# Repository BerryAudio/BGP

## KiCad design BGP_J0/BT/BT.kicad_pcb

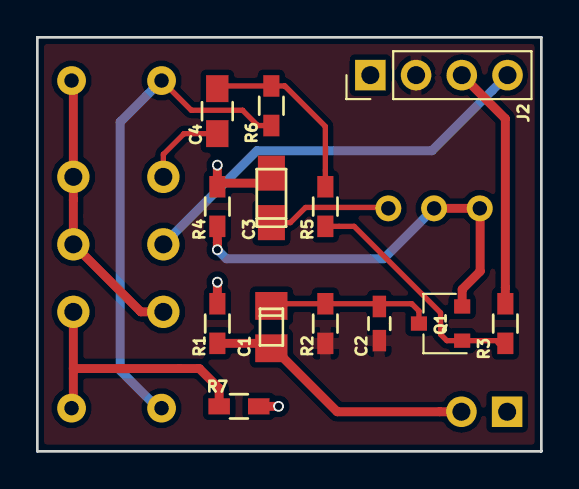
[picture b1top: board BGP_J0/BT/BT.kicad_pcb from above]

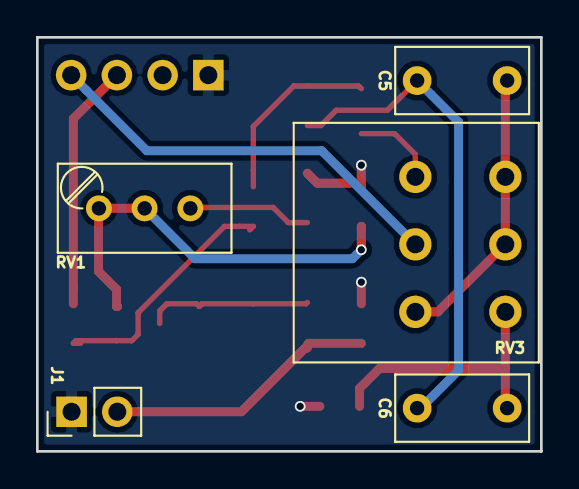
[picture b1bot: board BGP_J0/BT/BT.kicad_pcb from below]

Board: 2 copper layers, 28.0 x 23.0 mm, 18 parts (5 on the bottom side), 14 nets.

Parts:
C1: 0.1u; TantalC_SizeR_EIA-2012
C2: 270p; C_0603_HandSoldering
C3: 47u; TantalC_SizeS_EIA-3216
C4: 2700p; C_0805_HandSoldering
C5: 1u; C_Rect_L7.2mm_W3.5mm_P5.00mm_FKS2_FKP2_MKS2_MKP2
C6: 0.33u; C_Rect_L7.2mm_W3.5mm_P5.00mm_FKS2_FKP2_MKS2_MKP2
J1: Conn_01x02_Male; PinHeader_1x02_P2.54mm_Vertical
J2: Conn_01x04_Male; PinHeader_1x04_P2.54mm_Vertical
Q1: MMBF5457; SC-59
R1: NF; R_0603_HandSoldering
R2: 1Meg; R_0603_HandSoldering
R3, R6: 10k; R_0603_HandSoldering
R4: 3.9k; R_0603_HandSoldering
R5: 1k; R_0603_HandSoldering
R7: 1.8k; R_0603_HandSoldering
RV1: POT; Potentiometer_Trimmer_Bourns_3296W
RV3: DUAL_POT; Potentiometer_Alpha_Double_Vertical_Dual_Shaft

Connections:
/IN: C1.2, J1.2, R1.1
/RV_1: C6.2, R7.1, RV3.1
/RV_2: C5.2, RV3.2, RV3.3, RV3.4
/RV_5: J2.4, RV3.5
/RV_6: C4.2, RV3.6
/Vref: C2.2, J2.2, R2.2
Earth: C3.2, J1.1, J2.1, R1.2, R4.2, R7.2
unnamed: C1.1, C2.1, Q1.3, R2.1
unnamed: C3.1, RV1.3
unnamed: C4.1, R5.1, R6.1
unnamed: C5.1, C6.1, R6.2
unnamed: Q1.1, R3.2, R5.2
unnamed: Q1.2, R4.1, RV1.1, RV1.2
VCC: J2.3, R3.1

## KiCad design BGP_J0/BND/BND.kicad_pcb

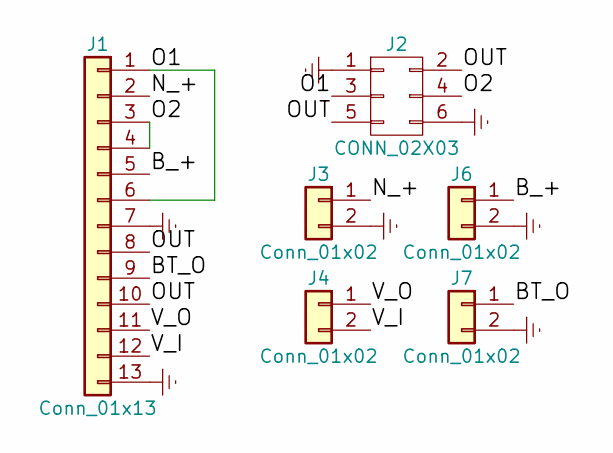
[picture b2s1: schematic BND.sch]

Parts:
J1: Conn_01x13; Bournes_Blend_PP
J2: CONN_02X03; Pin_Header_Straight_2x03
J3, J6: Conn_01x02; TerminalBlock_Phoenix_MPT-2.54mm_2pol
J4, J7: Conn_01x02; Pin_Header_Straight_1x02

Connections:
/BT_O: J1.9, J7.1
/B_+: J1.5, J6.1
/N_+: J1.2, J3.1
/O1: J1.1, J1.6, J2.3
/O2: J1.3, J1.4, J2.4
/OUT: J1.8, J1.10, J2.2, J2.5
/V_I: J1.12, J4.2
/V_O: J1.11, J4.1
Earth: J1.7, J1.13, J2.1, J2.6, J3.2, J6.2, J7.2

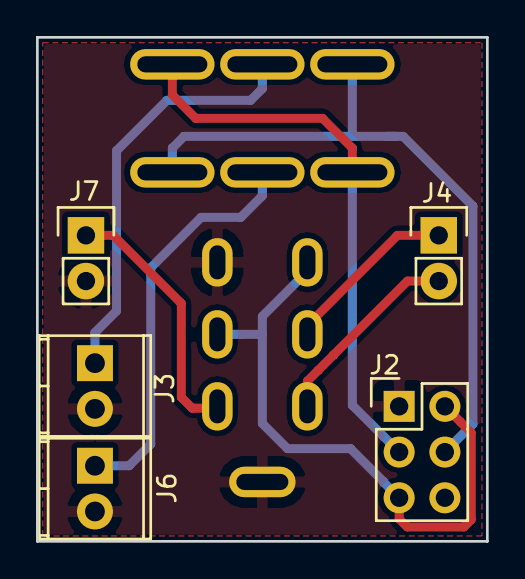
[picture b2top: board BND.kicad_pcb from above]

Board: 2 copper layers, 25.0 x 28.0 mm, 6 parts (1 on the bottom side), 9 nets.

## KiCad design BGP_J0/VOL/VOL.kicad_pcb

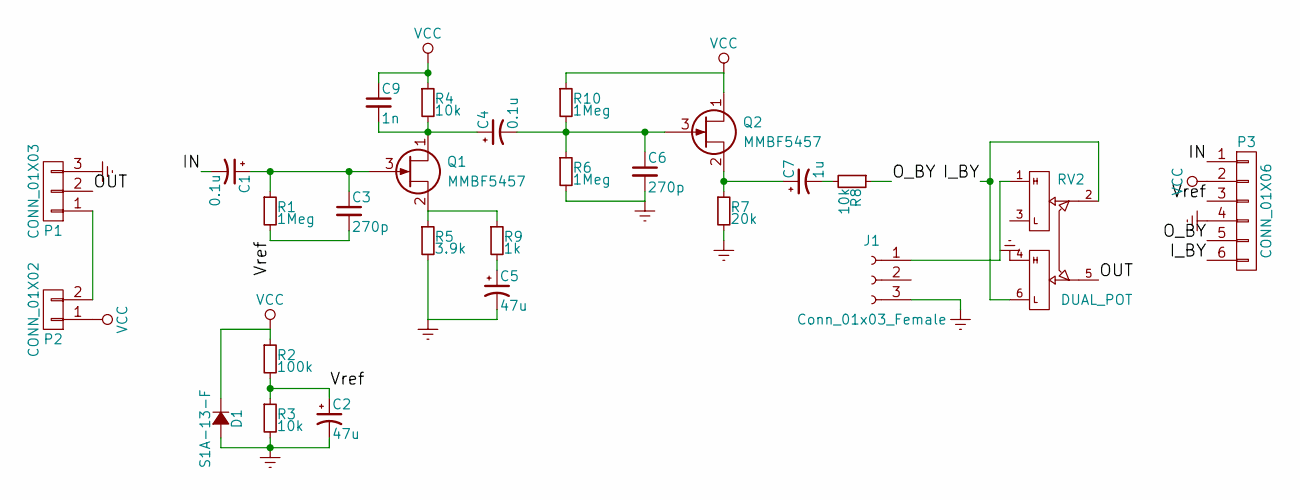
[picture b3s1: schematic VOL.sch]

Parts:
C1, C4: 0.1u; TantalC_SizeR_EIA-2012
C2, C5: 47u; TantalC_SizeS_EIA-3216
C3, C6: 270p; C_0603_HandSoldering
C7: 1u; TantalC_SizeR_EIA-2012
C9: 1n; C_0805
D1: S1A-13-F; SMA_Standard
J1: Conn_01x03_Female; Pin_Header_Straight_1x03_Pitch2.54mm
P1: CONN_01X03; TerminalBlock_Pheonix_MPT-2.54mm_3pol
P2: CONN_01X02; TerminalBlock_Pheonix_MPT-2.54mm_2pol
P3: CONN_01X06; Pin_Header_Straight_1x06
Q1, Q2: MMBF5457; SC-59
R1, R6, R10: 1Meg; R_0603_HandSoldering
R2: 100k; R_0603_HandSoldering
R3, R4, R8: 10k; R_0603_HandSoldering
R5: 3.9k; R_0603_HandSoldering
R7: 20k; R_0603_HandSoldering
R9: 1k; R_0603_HandSoldering
RV2: DUAL_POT; Potentiometer_Alpha_Double_Vertical_Dual_Shaft

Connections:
/IN: C1.2, P3.1
/I_BY: P3.6, RV2.2, RV2.6
/OUT: P1.2, RV2.5
/O_BY: P3.5, R8.1
/Vref: C2.1, C3.2, P3.3, R1.2, R2.2, R3.1
Earth: C2.2, C5.2, C6.2, D1.2 (A), J1.3, P1.3, P3.4, R3.2, R5.2, R6.2, R7.2, RV2.4
unnamed: C1.1, C3.1, Q1.3 (G), R1.1
unnamed: C4.1, C9.2, Q1.1 (D), R4.2
unnamed: C4.2, C6.1, Q2.3 (G), R6.1, R10.2
unnamed: C5.1, R9.2
unnamed: C7.1, Q2.2 (S), R7.1
unnamed: C7.2, R8.2
unnamed: J1.1, RV2.1
unnamed: P1.1, P2.2
unnamed: Q1.2 (S), R5.1, R9.1
VCC: C9.1, D1.1 (K), P2.1, P3.2, Q2.1 (D), R2.1, R4.1, R10.1

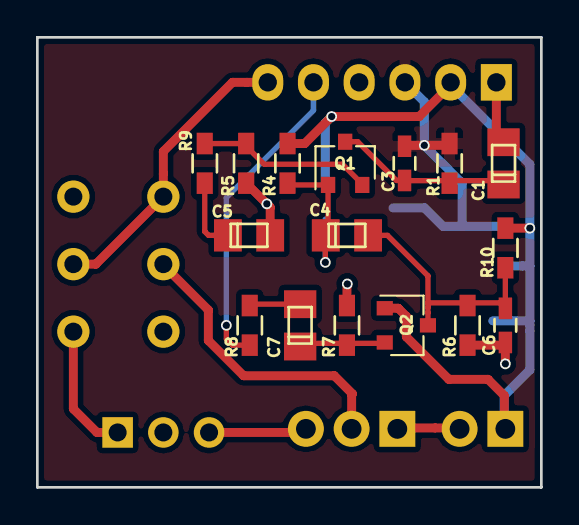
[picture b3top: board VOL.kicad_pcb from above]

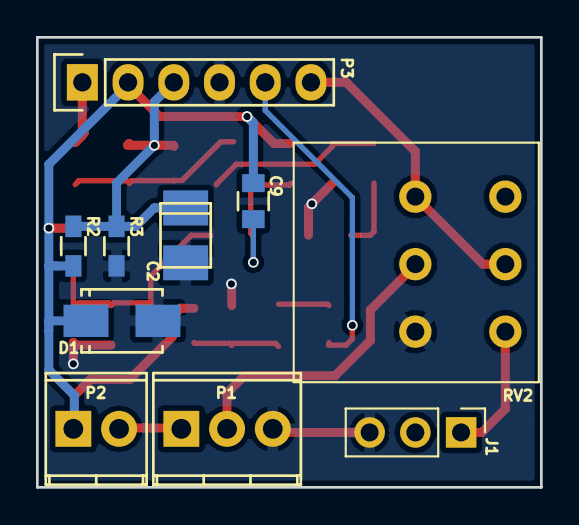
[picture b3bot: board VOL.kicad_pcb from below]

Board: 2 copper layers, 28.0 x 25.0 mm, 26 parts (10 on the bottom side), 16 nets.

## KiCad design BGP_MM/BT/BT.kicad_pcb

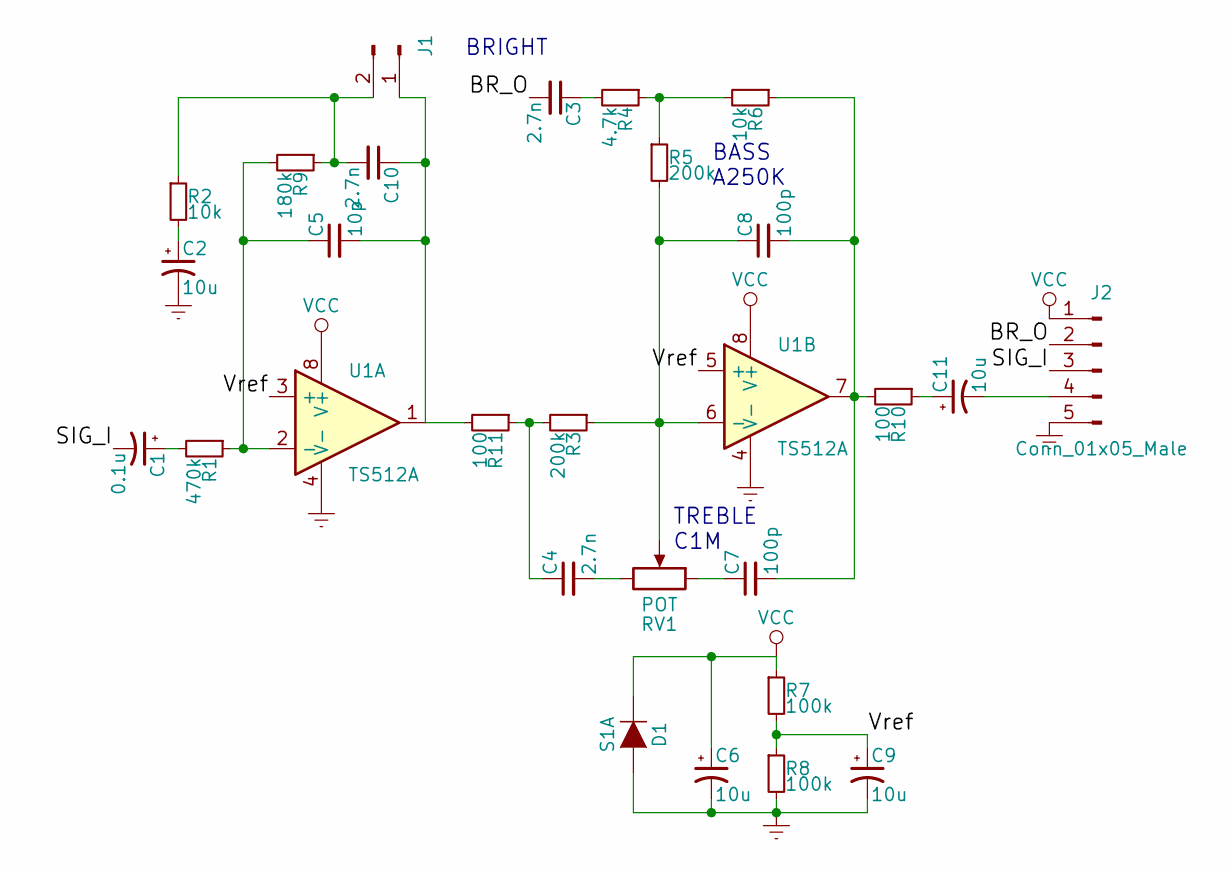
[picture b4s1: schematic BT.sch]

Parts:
C1: 0.1u; C_0805
C2, C11: 10u; C_0805
C3, C4, C10: 2.7n; C_0805
C5: 10p; C_0603_HandSoldering
C6, C9: 10u; C_1206
C7, C8: 100p; C_0603_HandSoldering
D1: S1A; SMA_Standard
J1: Conn_01x02_Male; Pin_Header_Straight_1x02
J2: Conn_01x05_Male; Pin_Header_Straight_1x05_Pitch2.54mm
R1: 470k; C_0603_HandSoldering
R2, R6: 10k; C_0603_HandSoldering
R3, R5: 200k; C_0603_HandSoldering
R4: 4.7k; C_0603_HandSoldering
R7, R8: 100k; C_0603_HandSoldering
R9: 180k; C_0603_HandSoldering
R10, R11: 100; C_0603_HandSoldering
RV1: POT; Potentiometer_Alpha_RV16
U1: TS512A; SOIC-8-N

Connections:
/BR_O: C3.2, J2.2
/SIG_I: C1.2, J2.3
/Vref: C9.1, R7.2, R8.1, U1.3 (+), U1.5 (+)
Earth: C2.2, C6.2, C9.2, D1.2 (A), J2.5, R8.2, U1.4 (V-)
unnamed: C1.1, R1.2
unnamed: C2.1, R2.2
unnamed: C3.1, R4.2
unnamed: C4.1, R3.2, R11.1
unnamed: C4.2, RV1.3
unnamed: C5.1, R1.1, R9.2, U1.2 (-)
unnamed: C7.1, RV1.1
unnamed: C7.2, C8.2, R6.1, R10.2, U1.7
unnamed: C8.1, R3.1, R5.2, RV1.2, U1.6 (-)
unnamed: C5.2, C10.1, J1.1, R11.2, U1.1
unnamed: C10.2, J1.2, R2.1, R9.1
unnamed: C11.1, R10.1
unnamed: C11.2, J2.4
unnamed: R4.1, R5.1, R6.2
VCC: C6.1, D1.1 (K), J2.1, R7.1, U1.8 (V+)

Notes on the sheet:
BRIGHT
BASS A250K
TREBLE C1M

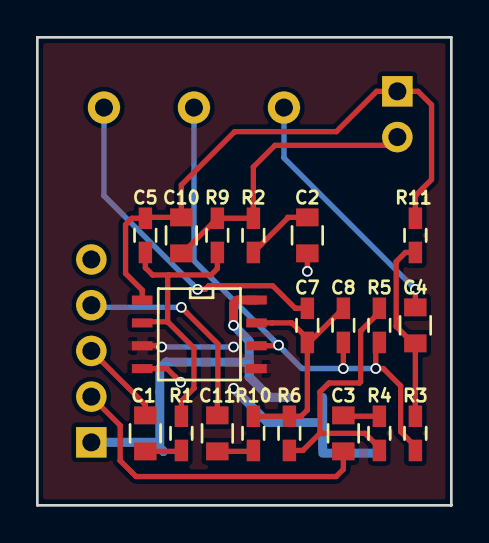
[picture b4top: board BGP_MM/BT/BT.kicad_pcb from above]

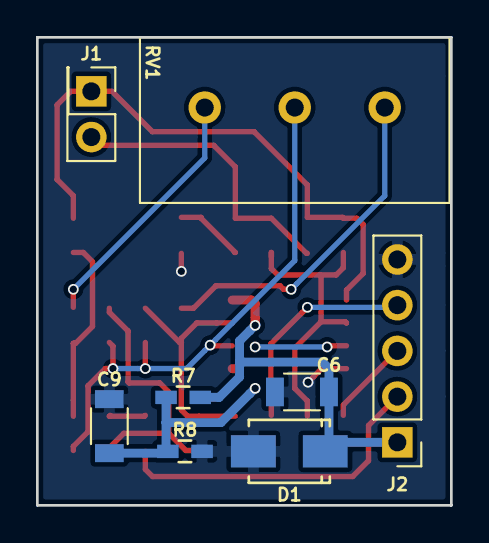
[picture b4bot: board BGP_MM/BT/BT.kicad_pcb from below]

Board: 2 copper layers, 23.0 x 26.0 mm, 27 parts (8 on the bottom side), 19 nets.

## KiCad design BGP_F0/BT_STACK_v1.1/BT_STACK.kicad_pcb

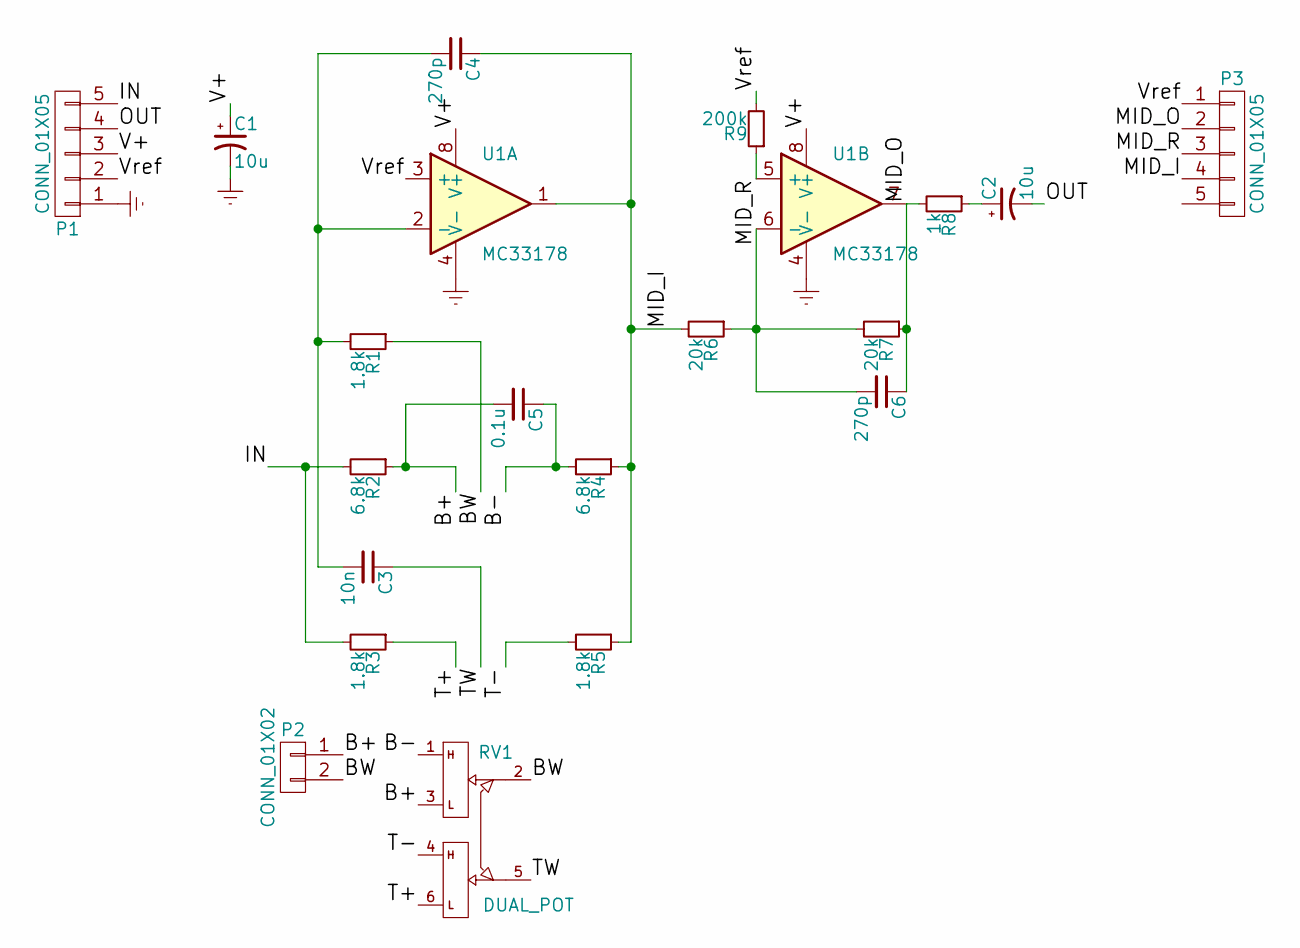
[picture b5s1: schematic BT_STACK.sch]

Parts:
C1: 10u; C_1206_HandSoldering
C2: 10u; C_0805_HandSoldering
C3: 10n; C_0805_HandSoldering
C4, C6: 270p; C_0603_HandSoldering
C5: 0.1u; C_0805_HandSoldering
P1, P3: CONN_01X05; Pin_Header_Straight_1x05
P2: CONN_01X02; Pin_Header_Straight_1x02_Pitch2.54mm
R1, R3, R5: 1.8k; R_0603_HandSoldering
R2, R4: 6.8k; R_0603_HandSoldering
R6, R7: 20k; R_0603_HandSoldering
R8: 1k; R_0603_HandSoldering
R9: 200k; R_0603_HandSoldering
RV1: DUAL_POT; Potentiometer_Alpha_Double_Vertical_Dual_Shaft
U1: MC33178; SOIC-8_3.9x4.9mm_Pitch1.27mm

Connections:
/B+: C5.2, P2.1, R2.1, RV1.3
/B-: C5.1, R4.2, RV1.1
/BW: P2.2, R1.1, RV1.2
/IN: P1.5, R2.2, R3.2
/MID_I: C4.1, P3.4, R4.1, R5.1, R6.2, U1.1
/MID_O: C6.1, P3.2, R7.1, R8.2, U1.7
/MID_R: P3.3, R9.1, U1.5 (+)
/OUT: C2.2, P1.4
/T+: R3.1, RV1.6
/T-: R5.2, RV1.4
/TW: C3.1, RV1.5
/V+: C1.1, P1.3, U1.8 (V+)
/Vref: P1.2, P3.1, R9.2, U1.3 (+)
Earth: C1.2, P1.1, U1.4 (V-)
unnamed: C2.1, R8.1
unnamed: C3.2, C4.2, R1.2, U1.2 (-)
unnamed: C6.2, R6.1, R7.2, U1.6 (-)

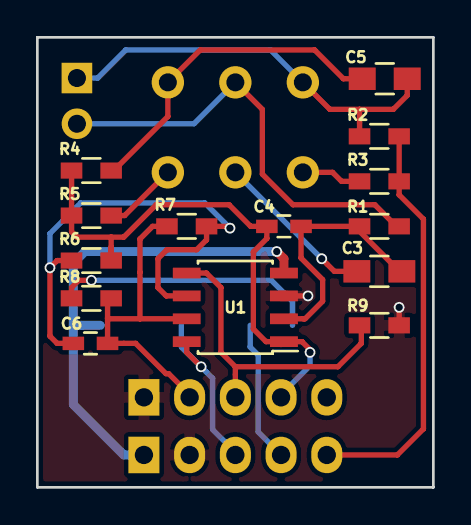
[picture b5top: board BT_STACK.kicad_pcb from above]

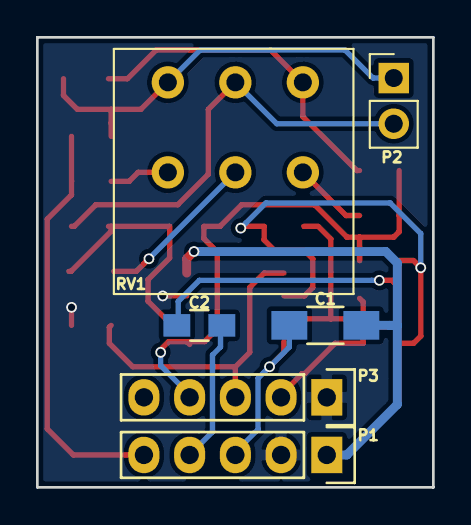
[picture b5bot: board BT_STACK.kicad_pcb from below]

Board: 2 copper layers, 22.0 x 25.0 mm, 20 parts (6 on the bottom side), 17 nets.

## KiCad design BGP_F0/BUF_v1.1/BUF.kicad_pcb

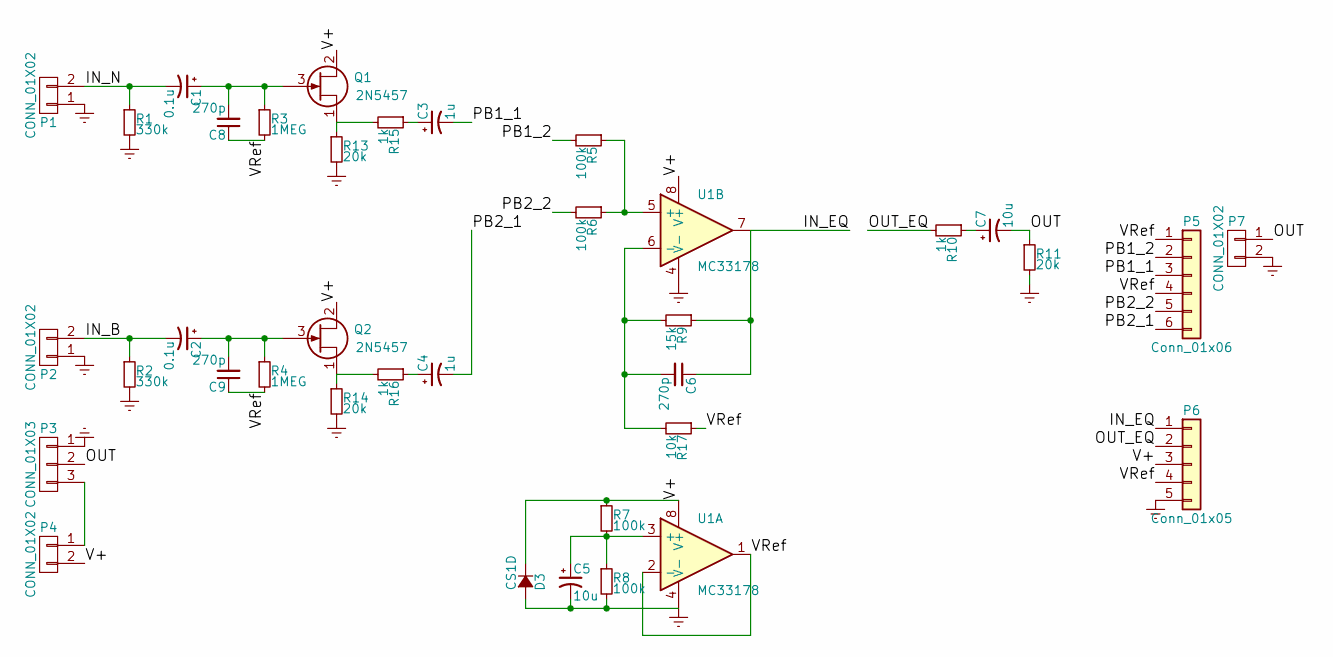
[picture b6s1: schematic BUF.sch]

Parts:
C1, C2: 0.1u; C_0805
C3, C4: 1u; C_0805
C5: 10u; C_1206
C6, C8, C9: 270p; C_0603
C7: 10u; C_0805
D3: CS1D; D_SMA
P1, P2, P4: CONN_01X02; TerminalBlock_Pheonix_MPT-2.54mm_2pol
P3: CONN_01X03; TerminalBlock_Pheonix_MPT-2.54mm_3pol
P5: Conn_01x06; Potentiometer_Alpha_Double_Vertical_Dual_Shaft
P6: Conn_01x05; Pin_Header_Straight_1x05
P7: CONN_01X02; Pin_Header_Straight_1x02
Q1, Q2: 2N5457; SC-59
R1, R2: 330k; R_0603
R3, R4: 1MEG; R_0603
R5, R6, R7, R8: 100k; R_0603
R9: 15k; R_0603
R10, R15, R16: 1k; R_0603
R11, R13, R14: 20k; R_0603
R17: 10k; R_0603
U1: MC33178; SOIC-8_3.9x4.9mm_Pitch1.27mm

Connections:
/IN_B: C2.2, P2.2, R2.1
/IN_EQ: C6.1, P6.1, R9.1, U1.7
/IN_N: C1.2, P1.2, R1.1
/OUT: C7.2, P3.2, P7.1, R11.1
/OUT_EQ: P6.2, R10.2
/PB1_1: C3.2, P5.3
/PB1_2: P5.2, R5.2
/PB2_1: C4.2, P5.6
/PB2_2: P5.5, R6.2
/V+: D3.1 (K), P4.2, P6.3, Q1.2 (D), Q2.2 (D), R7.1, U1.8 (V+)
/VRef: C8.1, C9.1, P5.1, P5.4, P6.4, R3.2, R4.2, R17.1, U1.1, U1.2 (-)
Earth: C5.2, D3.2 (A), P1.1, P2.1, P3.1, P6.5, P7.2, R1.2, R2.2, R8.2, R11.2, R13.2, R14.2, U1.4 (V-)
unnamed: C1.1, C8.2, Q1.3 (G), R3.1
unnamed: C2.1, C9.2, Q2.3 (G), R4.1
unnamed: C3.1, R15.1
unnamed: C4.1, R16.1
unnamed: C5.1, R7.2, R8.1, U1.3 (+)
unnamed: C6.2, R9.2, R17.2, U1.6 (-)
unnamed: C7.1, R10.1
unnamed: P3.3, P4.1
unnamed: Q1.1 (S), R13.1, R15.2
unnamed: Q2.1 (S), R14.1, R16.2
unnamed: R5.1, R6.1, U1.5 (+)

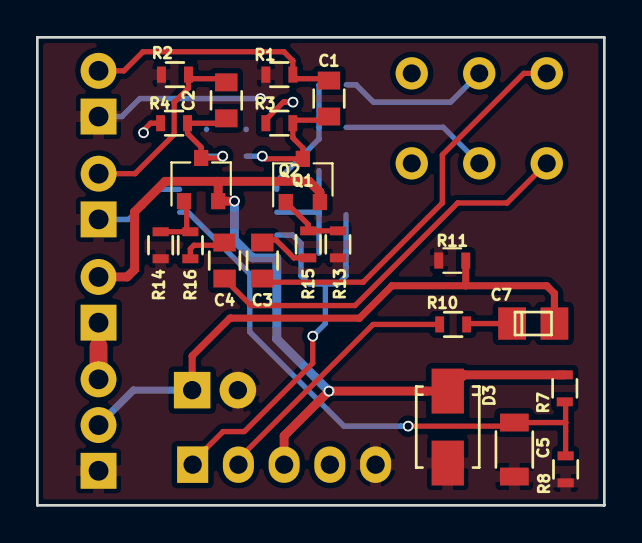
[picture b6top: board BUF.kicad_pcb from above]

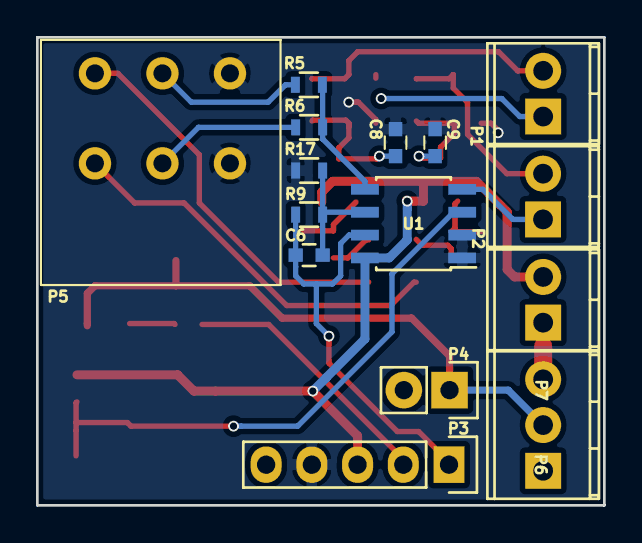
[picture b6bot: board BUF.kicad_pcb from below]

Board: 2 copper layers, 31.5 x 26.0 mm, 36 parts (15 on the bottom side), 23 nets.

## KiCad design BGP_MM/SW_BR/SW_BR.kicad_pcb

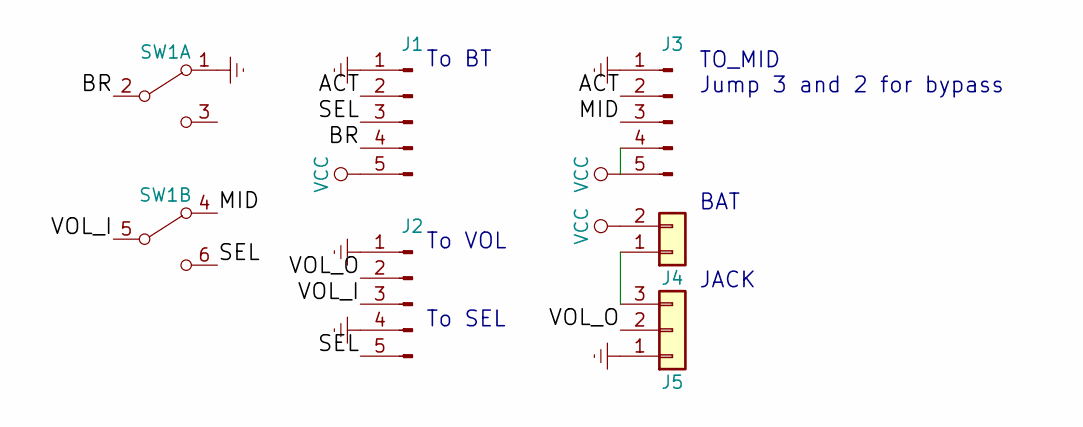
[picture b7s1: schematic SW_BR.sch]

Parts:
J1, J2, J3: Conn_01x05_Male; Pin_Header_Straight_1x05_Pitch2.54mm
J4: Conn_01x02; TerminalBlock_Phoenix_MPT-2.54mm_2pol
J5: Conn_01x03; TerminalBlock_Phoenix_MPT-2.54mm_3pol
SW1: SW_DPDT; NKK_DPDT

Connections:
/ACT: J1.2, J3.2
/BR: J1.4, SW1.2 (B)
/MID: J3.3, SW1.4 (A)
/SEL: J1.3, J2.5, SW1.6 (C)
/VOL_I: J2.3, SW1.5 (B)
/VOL_O: J2.2, J5.2
Earth: J1.1, J2.1, J2.4, J3.1, J5.1, SW1.1 (A)
unnamed: J4.1, J5.3
VCC: J1.5, J3.4, J3.5, J4.2

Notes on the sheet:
To BT
To SEL
To VOL
TO_MID Jump 3 and 2 for bypass
BAT
JACK

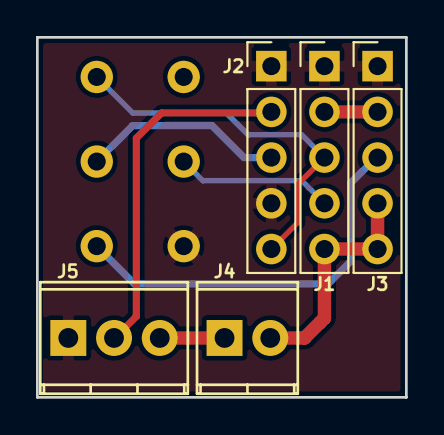
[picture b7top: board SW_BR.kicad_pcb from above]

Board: 2 copper layers, 20.5 x 20.0 mm, 6 parts (1 on the bottom side), 9 nets.

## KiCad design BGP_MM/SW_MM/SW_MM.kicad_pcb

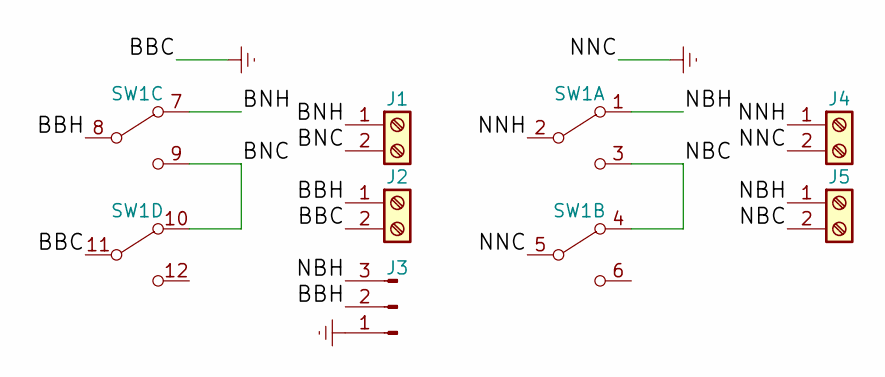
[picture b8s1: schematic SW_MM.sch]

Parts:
J1, J2, J4, J5: Screw_Terminal_01x02; TerminalBlock_Phoenix_MPT-2.54mm_2pol
J3: Conn_01x03_Male; Pin_Header_Straight_1x03_Pitch2.54mm
SW1: SW_4PDT; NKK_DP3T

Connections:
/BBH: J2.1, J3.2, SW1.8 (B)
/BNC: J1.2, SW1.9 (C), SW1.10 (A)
/BNH: J1.1, SW1.7 (A)
/NBC: J5.2, SW1.3 (C), SW1.4 (A)
/NBH: J3.3, J5.1, SW1.1 (A)
/NNH: J4.1, SW1.2 (B)
Earth: J2.2, J3.1, J4.2, SW1.5 (B), SW1.11 (B)
